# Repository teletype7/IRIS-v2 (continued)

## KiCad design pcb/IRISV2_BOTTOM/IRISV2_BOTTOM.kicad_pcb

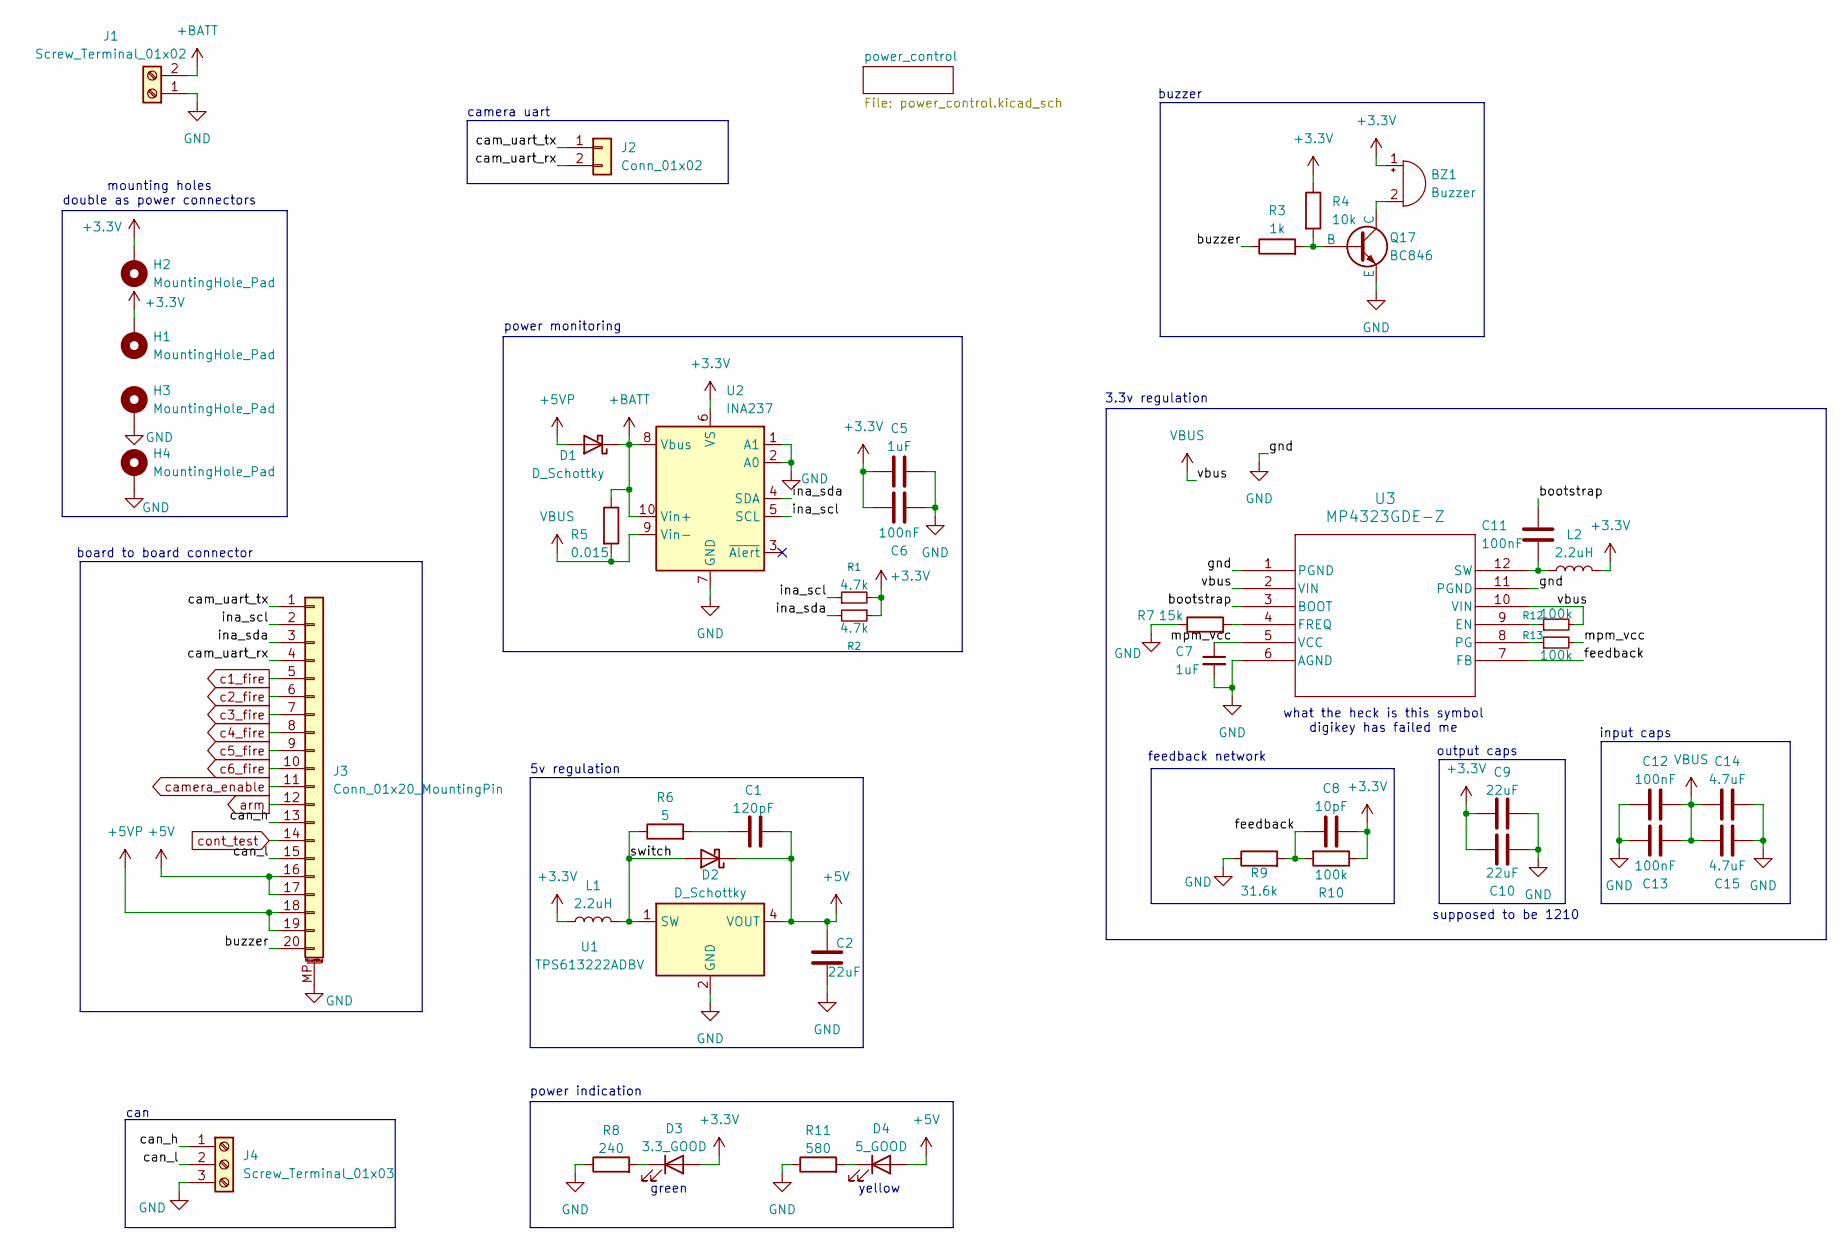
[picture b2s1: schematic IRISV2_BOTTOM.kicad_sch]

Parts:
BZ1: Buzzer; CMT850403SMTTR
C1: 120pF; C_0603_1608Metric
C2: 22uF; C_1206_3216Metric
C5, C7: 1uF; C_0603_1608Metric
C6: 100nF; C_0402_1005Metric
C8: 10pF; C_0402_1005Metric
C9, C10: 22uF; C_1210_3225Metric
C11, C12, C13: 100nF; C_0603_1608Metric
C14, C15: 4.7uF; C_1210_3225Metric
D1, D2: D_Schottky; DIOM5027X240N
D3: 3.3_GOOD; LED_0805_2012Metric
D4: 5_GOOD; LED_0805_2012Metric
H1, H2, H3, H4: MountingHole_Pad; MountingHole_3.2mm_M3_ISO7380_Pad_TopBottom
J1: Screw_Terminal_01x02; kf350-2p
J2: Conn_01x02; PinHeader_1x02_P2.54mm_Vertical
J3: Conn_01x20_MountingPin; FFC3B07-20-T
J4: Screw_Terminal_01x03; OSTTE030104
L1: 2.2uH; L_1008_2520Metric
L2: 2.2uH; SRP5020TA2R2M
Q17: BC846; SOT-23-3
R1, R2: 4.7k; R_0402_1005Metric
R3: 1k; R_0402_1005Metric
R4: 10k; R_0402_1005Metric
R5: 0.015; R_2512_6332Metric
R6: 5; R_0603_1608Metric
R7: 15k; R_0402_1005Metric
R8: 240; R_0603_1608Metric
R9: 31.6k; R_0402_1005Metric
R10, R12, R13: 100k; R_0402_1005Metric
R11: 580; R_0603_1608Metric
U1: TPS613222ADBV; SOT-23-5
U2: INA237; VSSOP-10_3x3mm_P0.5mm
U3: MP4323GDE-Z; QFN-12_MP4323_MNP

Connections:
+3.3V: BZ1.1 (+), C5.1, C6.2, C8.2, C9.1, C10.2, D3.2 (A), H1.1, H2.1, L1.1, L2.2, R1.2, R2.1, R4.1, R10.1, U2.6 (VS); also elsewhere on the board
+5V: C1.2, C2.1, D2.1 (K), D4.2 (A), J3.16, J3.17, U1.4 (VOUT)
+5VP: D1.2 (A), J3.18, J3.19
+BATT: D1.1 (K), J1.2, R5.1, U2.8 (Vbus), U2.10 (Vin+); also elsewhere on the board
/bootstrap: C11.1, U3.3 (BOOT)
/buzzer: J3.20, R3.1
/cam_uart_rx: J2.2, J3.4
/cam_uart_tx: J2.1, J3.1
/can_h: J3.13, J4.1
/can_l: J3.15, J4.2
/feedback: C8.1, R9.2, R10.2, U3.7 (FB)
/ina_scl: J3.2, R1.1, U2.5 (SCL)
/ina_sda: J3.3, R2.2, U2.4 (SDA)
/mpm_vcc: C7.1, R13.2, U3.5 (VCC)
/switch: D2.2 (A), L1.2, R6.1, U1.1 (SW)
GND: C2.2, C5.2, C6.1, C7.2, C9.2, C10.1, C12.1, C13.2, C14.2, C15.1, H3.1, H4.1, J1.1, J3.MP (MountPin), J4.3, Q17.3 (E), R7.1, R8.1, R9.1, R11.1, U1.2 (GND), U2.1 (A1), U2.2 (A0), U2.7 (GND), U3.1 (PGND), U3.6 (AGND), U3.11 (PGND); also elsewhere on the board
unnamed: BZ1.2 (-), Q17.1 (C)
unnamed: C1.1, R6.2
unnamed: D3.1 (K), R8.2
unnamed: D4.1 (K), R11.2
unnamed: Q17.2 (B), R3.2, R4.2
unnamed: R12.1, U3.9 (EN)
unnamed: R7.2, U3.4 (FREQ)
unnamed: R13.1, U3.8 (PG)
unnamed: C11.2, L2.1, U3.12 (SW)
VBUS: C12.2, C13.1, C14.1, C15.2, R5.2, R12.2, U2.9 (Vin-), U3.2 (VIN), U3.10 (VIN); also elsewhere on the board
arm: J3.12; also elsewhere on the board
c1_fire: J3.5; also elsewhere on the board
c2_fire: J3.6; also elsewhere on the board
c3_fire: J3.7; also elsewhere on the board
c4_fire: J3.8; also elsewhere on the board
c5_fire: J3.9; also elsewhere on the board
c6_fire: J3.10; also elsewhere on the board
camera_enable: J3.11; also elsewhere on the board
cont_test: J3.14; also elsewhere on the board

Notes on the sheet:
power monitoring
input caps
supposed to be 1210
power indication
camera uart
green
3.3v regulation
yellow
5v regulation
can
output caps
buzzer
board to board connector
what the heck is this symbol digikey has failed me
feedback network
mounting holes double as power connectors

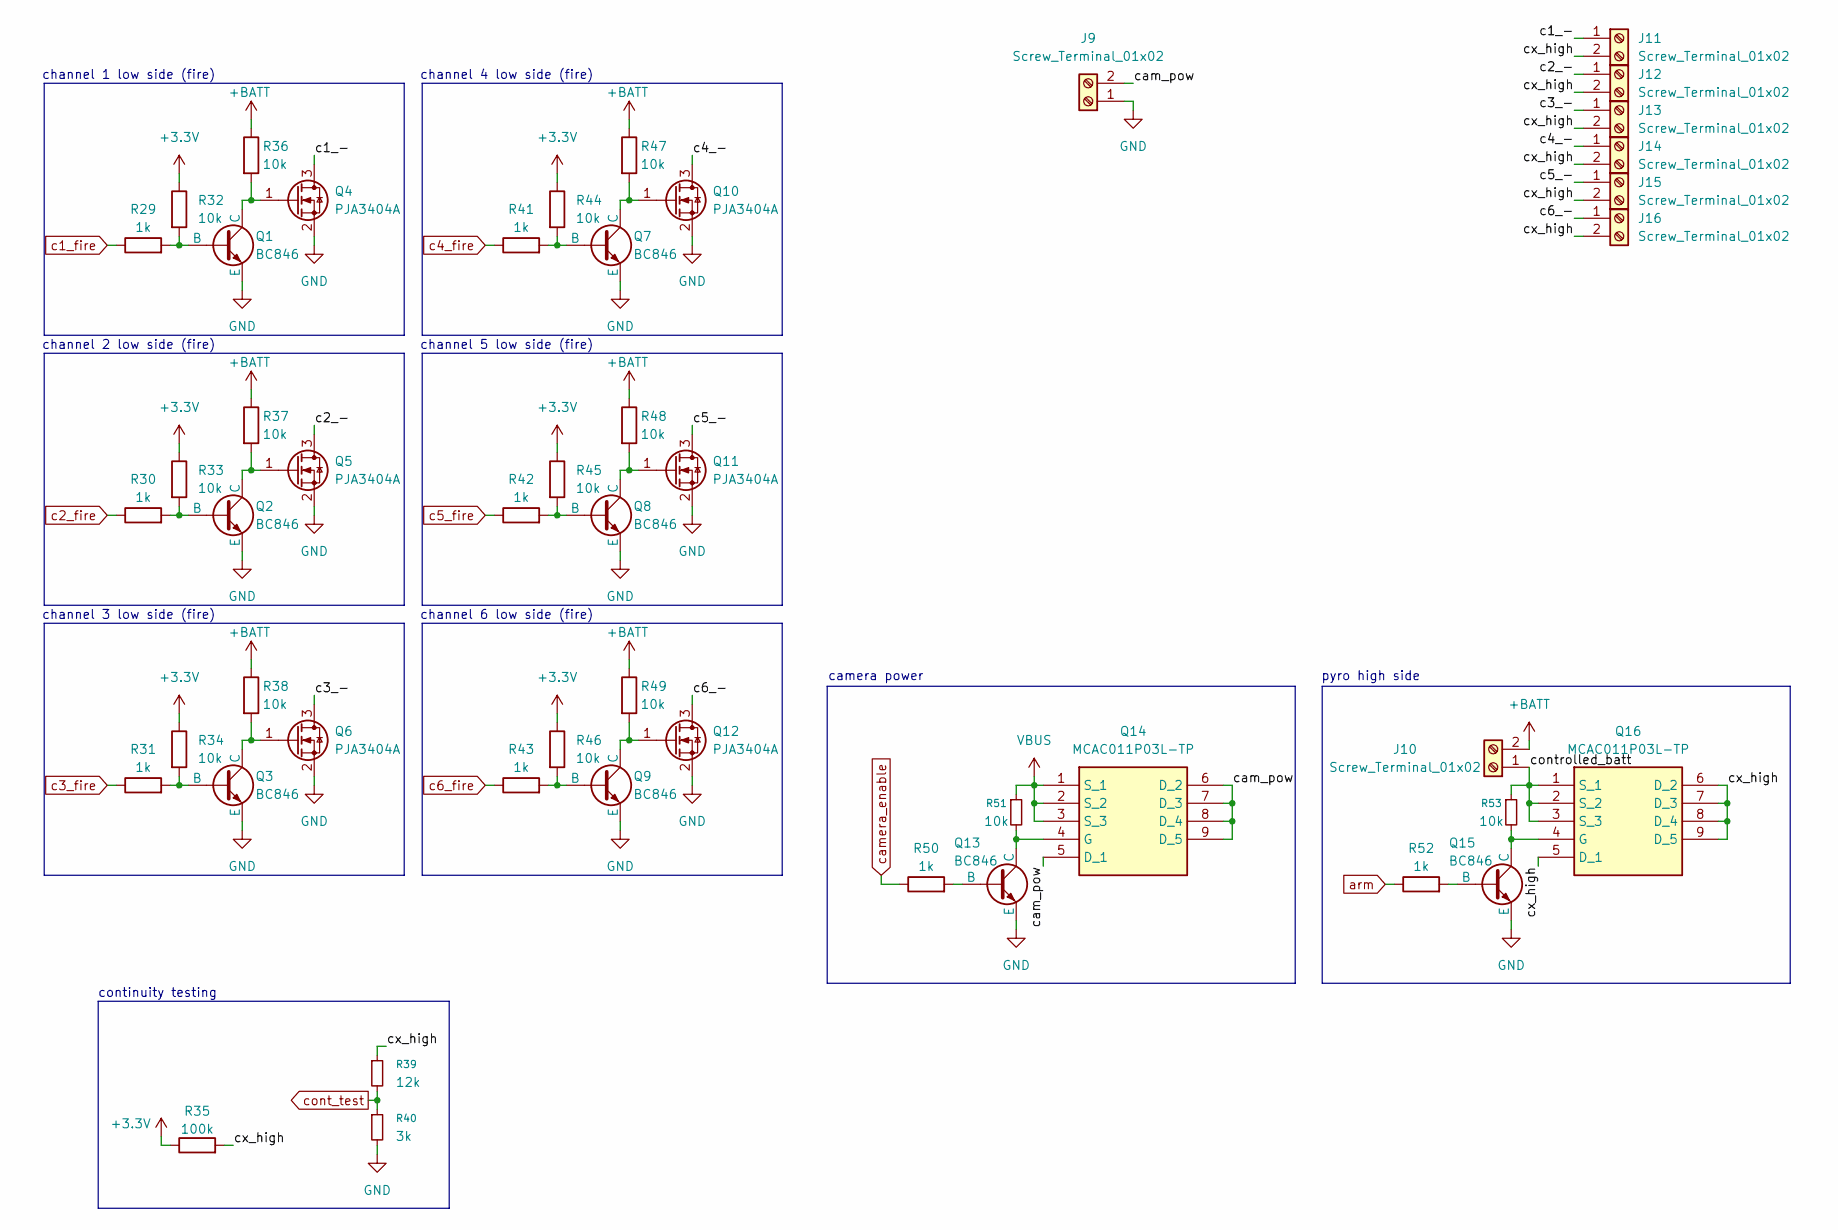
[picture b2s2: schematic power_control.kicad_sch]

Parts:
J9, J10, J11, J12, J13, J14, J15, J16: Screw_Terminal_01x02; kf350-2p
Q1, Q2, Q3, Q7, Q8, Q9, Q13, Q15: BC846; SOT-23-3
Q4, Q5, Q6, Q10, Q11, Q12: PJA3404A; SOT-23-3
Q14, Q16: MCAC011P03L-TP; MCAC100N08YATP; Manufacturer_Part_Number MCAC011P03L-TP
R29, R30, R31, R41, R42, R43, R50, R52: 1k; R_0402_1005Metric
R32, R33, R34, R36, R37, R38, R44, R45, R46, R47, R48, R49, R51, R53: 10k; R_0402_1005Metric
R35: 100k; R_0402_1005Metric
R39: 12k; R_0402_1005Metric
R40: 3k; R_0402_1005Metric

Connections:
+3.3V: R32.1, R33.1, R34.1, R35.1, R44.1, R45.1, R46.1; also elsewhere on the board
+BATT: J10.2, R36.1, R37.1, R38.1, R47.1, R48.1, R49.1; also elsewhere on the board
/power_control/c1_-: J11.1, Q4.3 (D)
/power_control/c2_-: J12.1, Q5.3 (D)
/power_control/c3_-: J13.1, Q6.3 (D)
/power_control/c4_-: J14.1, Q10.3 (D)
/power_control/c5_-: J15.1, Q11.3 (D)
/power_control/c6_-: J16.1, Q12.3 (D)
/power_control/cam_pow: J9.2, Q14.5 (D_1), Q14.6 (D_2), Q14.7 (D_3), Q14.8 (D_4), Q14.9 (D_5)
/power_control/controlled_batt: J10.1, Q16.1 (S_1), Q16.2 (S_2), Q16.3 (S_3), R53.1
/power_control/cx_high: J11.2, J12.2, J13.2, J14.2, J15.2, J16.2, Q16.5 (D_1), Q16.6 (D_2), Q16.7 (D_3), Q16.8 (D_4), Q16.9 (D_5), R35.2, R39.1
GND: J9.1, Q1.3 (E), Q2.3 (E), Q3.3 (E), Q4.2 (S), Q5.2 (S), Q6.2 (S), Q7.3 (E), Q8.3 (E), Q9.3 (E), Q10.2 (S), Q11.2 (S), Q12.2 (S), Q13.3 (E), Q15.3 (E), R40.2; also elsewhere on the board
unnamed: Q1.2 (B), R29.2, R32.2
unnamed: Q1.1 (C), Q4.1 (G), R36.2
unnamed: Q2.2 (B), R30.2, R33.2
unnamed: Q2.1 (C), Q5.1 (G), R37.2
unnamed: Q3.2 (B), R31.2, R34.2
unnamed: Q3.1 (C), Q6.1 (G), R38.2
unnamed: Q7.2 (B), R41.2, R44.2
unnamed: Q8.2 (B), R42.2, R45.2
unnamed: Q9.2 (B), R43.2, R46.2
unnamed: Q7.1 (C), Q10.1 (G), R47.2
unnamed: Q8.1 (C), Q11.1 (G), R48.2
unnamed: Q9.1 (C), Q12.1 (G), R49.2
unnamed: Q13.2 (B), R50.2
unnamed: Q13.1 (C), Q14.4 (G), R51.2
unnamed: Q15.2 (B), R52.2
unnamed: Q15.1 (C), Q16.4 (G), R53.2
VBUS: Q14.1 (S_1), Q14.2 (S_2), Q14.3 (S_3), R51.1; also elsewhere on the board
arm: R52.1; also elsewhere on the board
c1_fire: R29.1; also elsewhere on the board
c2_fire: R30.1; also elsewhere on the board
c3_fire: R31.1; also elsewhere on the board
c4_fire: R41.1; also elsewhere on the board
c5_fire: R42.1; also elsewhere on the board
c6_fire: R43.1; also elsewhere on the board
camera_enable: R50.1; also elsewhere on the board
cont_test: R39.2, R40.1; also elsewhere on the board

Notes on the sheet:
channel 6 low side (fire)
channel 2 low side (fire)
channel 1 low side (fire)
pyro high side
camera power
continuity testing
channel 4 low side (fire)
channel 5 low side (fire)
channel 3 low side (fire)

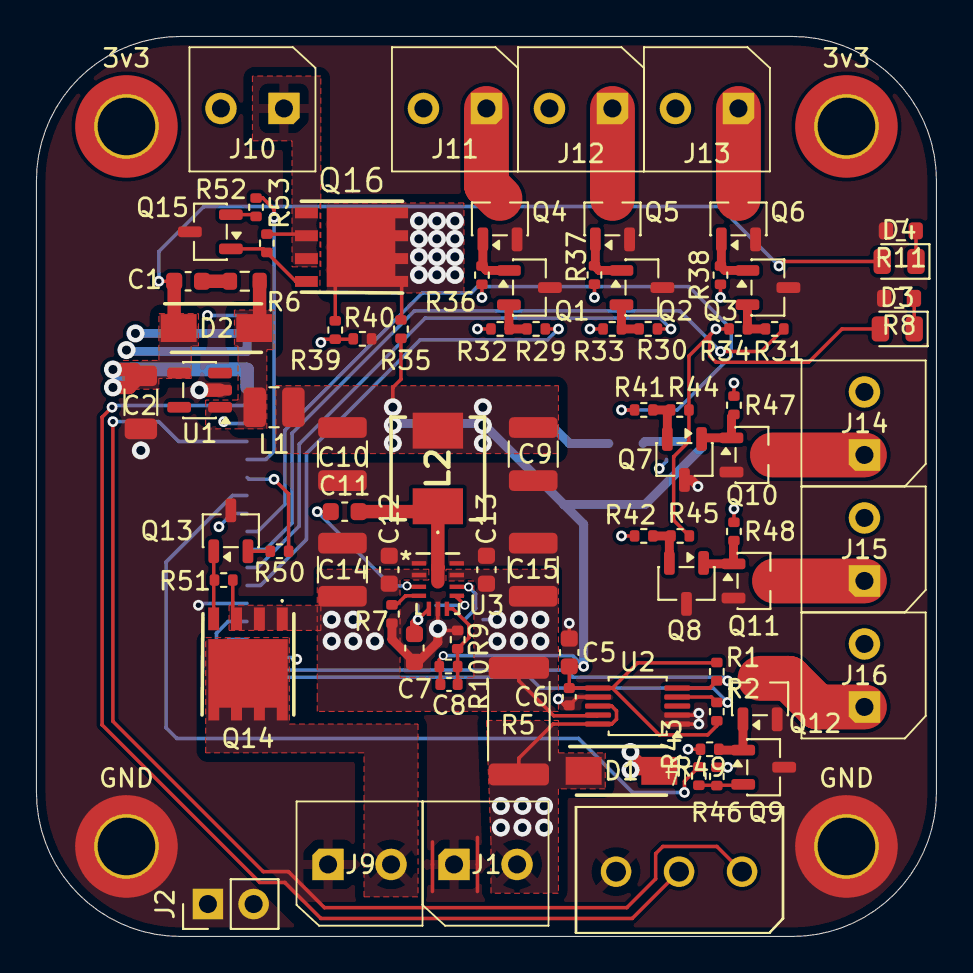
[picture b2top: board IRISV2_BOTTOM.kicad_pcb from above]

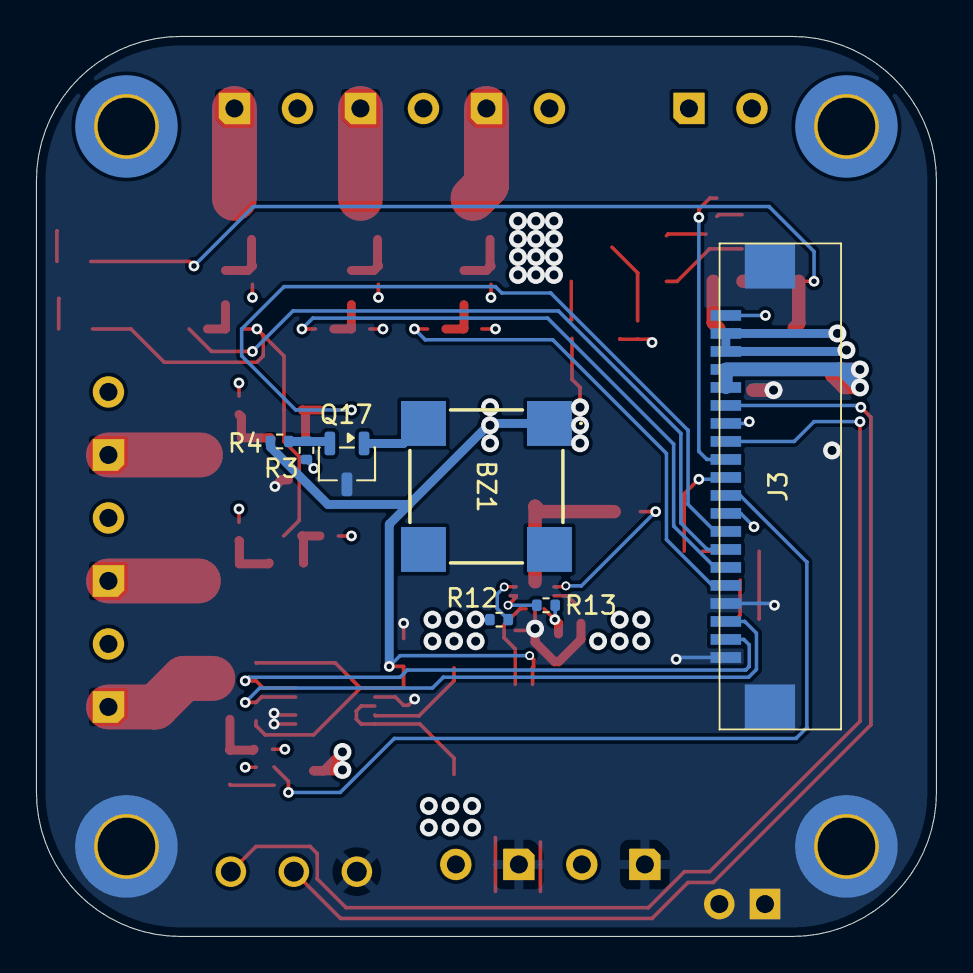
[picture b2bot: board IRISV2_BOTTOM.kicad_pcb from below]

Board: 4 copper layers, 50.0 x 50.0 mm, 94 parts (7 on the bottom side), 60 nets.

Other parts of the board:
3v3, 3v3#2: MountingHole_Pad; MountingHole_3.2mm_M3_ISO7380_Pad_TopBottom
GND: MountingHole_Pad; MountingHole_3.2mm_M3_ISO7380_Pad_TopBottom
GND#2: MountingHole_Pad; MountingHole_3.2mm_M3_ISO7380_Pad_TopBottom

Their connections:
+3.3V: 3v3.1, 3v3#2.1; also elsewhere on the board
GND: GND.1, GND#2.1; also elsewhere on the board

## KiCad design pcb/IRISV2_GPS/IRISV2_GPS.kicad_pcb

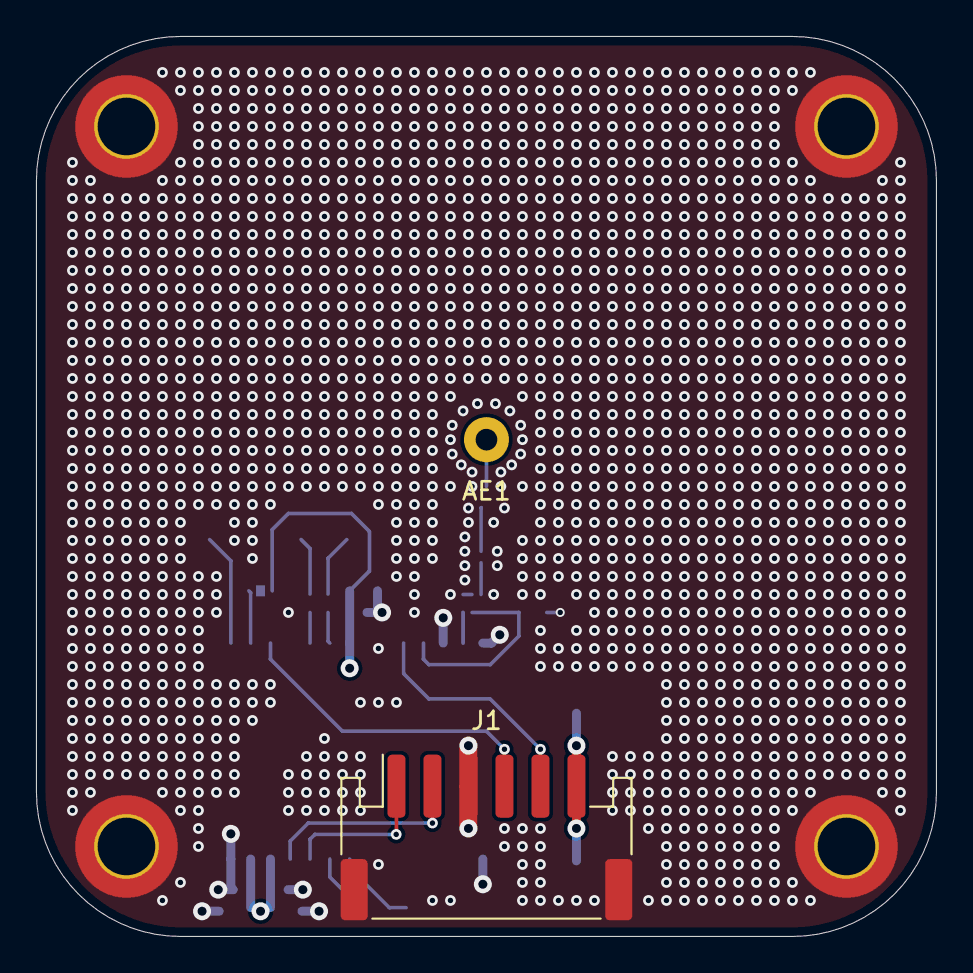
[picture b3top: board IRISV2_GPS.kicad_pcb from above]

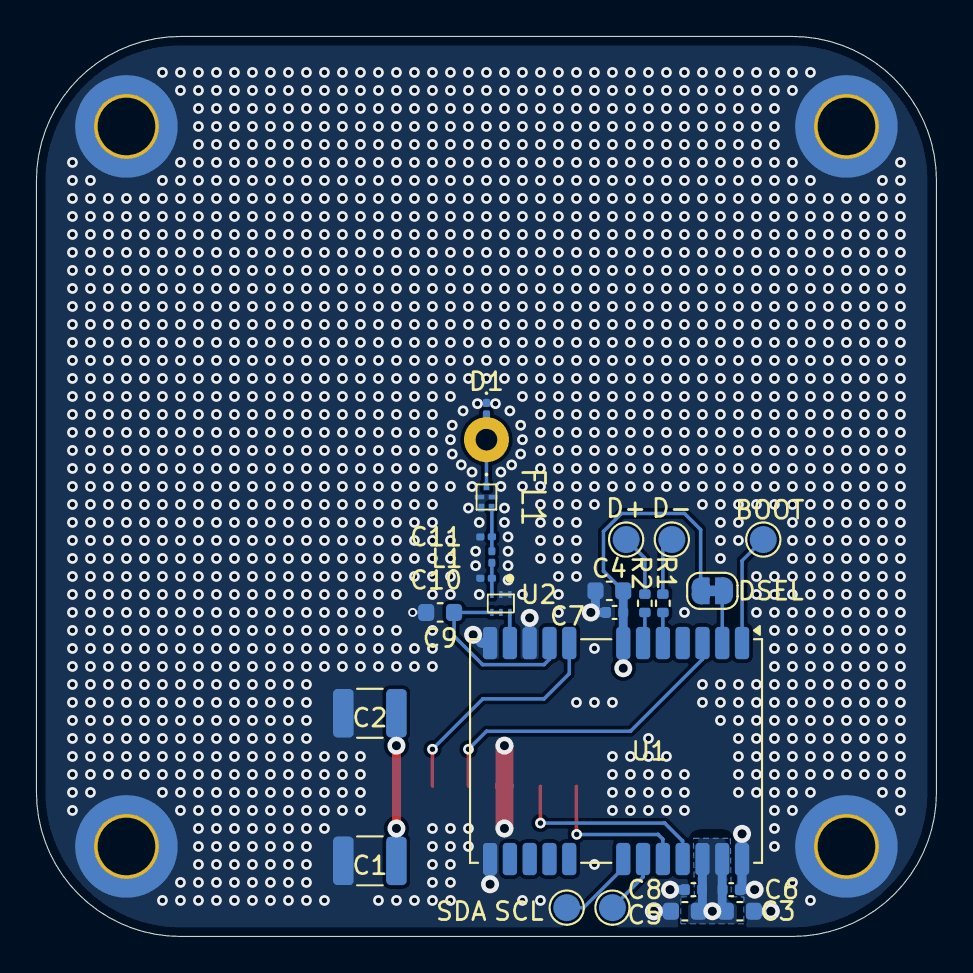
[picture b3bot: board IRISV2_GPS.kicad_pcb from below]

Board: 4 copper layers, 50.0 x 50.0 mm, 30 parts (24 on the bottom side), 19 nets.

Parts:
AE1: AANI-PP-0055
BOOT: GPS_BOOT; TestPoint_Pad_D1.5mm
C1, C2: 22uF; C_1210_3225Metric
C3, C4, C5, C9: 1uF; C_0603_1608Metric
C6, C7, C8: 100nF; C_0402_1005Metric
C10, C11: dnp; C_0201_0603Metric
D1: D_TVS; D_0201_0603Metric
D+: GPS_D+; TestPoint_Pad_D1.5mm
D-: GPS_D-; TestPoint_Pad_D1.5mm
DSEL: NC; SolderJumper-2_P1.3mm_Bridged_RoundedPad1.0x1.5mm
FL1: AFII-SW-0061-T; AFIISW0061T
H1, H2, H3, H4: MountingHole_Pad; MountingHole_3.2mm_M3_ISO7380_Pad_TopBottom
J1: Conn_01x06_MountingPin; JST_PH_S6B-PH-SM4-TB_1x06-1MP_P2.00mm_Horizontal
L1: 9.1nH; L_0201_0603Metric
R1, R2: 22; R_0402_1005Metric
SCL: GPS_SCL; TestPoint_Pad_D1.5mm
SDA: GPS_SDA; TestPoint_Pad_D1.5mm
U1: NEO-M9N; ublox_NEO
U2: lna; ALND-WB-0013-T

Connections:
+3.3V: C1.1, C2.1, C3.1, C4.1, C5.1, C6.1, C7.1, C8.1, DSEL.1 (A), J1.6, U1.7 (VDD_USB), U1.22 (V_BCKP), U1.23 (VCC)
GND: C1.2, C2.2, C3.2, C4.2, C5.2, C6.2, C7.2, C8.2, C9.2, C10.1, C11.2, D1.1 (A1), FL1.2 (GND), H1.1, H2.1, H3.1, H4.1, J1.3, J1.MP (MountPin), U1.10 (GND), U1.12 (GND), U1.13 (GND), U1.24 (GND), U2.1 (GND), U2.2 (GND)
unnamed: AE1.1 (A), D1.2 (A2), FL1.1 (INPUT)
unnamed: C11.1, FL1.4 (OUTPUT), L1.2
unnamed: DSEL.2 (B), U1.2 (D_SEL)
unnamed: D-.1, R1.1
unnamed: D+.1, R2.2
unnamed: U1.11 (RF_IN), U2.6 (RFOUT)
unnamed: SCL.1, U1.19 (SCL/SPI_CLK)
unnamed: SDA.1, U1.18 (SDA/~SPI_CS)
unnamed: R1.2, U1.5 (USB_DM)
unnamed: R2.1, U1.6 (USB_DP)
unnamed: C9.1, U1.9 (VCC_RF), U2.4 (VDD), U2.5 (Ven)
unnamed: BOOT.1, U1.1 (~SAFEBOOT)
unnamed: C10.2, L1.1, U2.3 (RFIN)
gps_mrx: J1.1, U1.20 (TXD/SPI_MISO)
gps_mtx: J1.2, U1.21 (RXD/SPI_MOSI)
gps_pps: J1.4, U1.3 (TIMEPULSE)
gps_rst: J1.5, U1.8 (~RESET)

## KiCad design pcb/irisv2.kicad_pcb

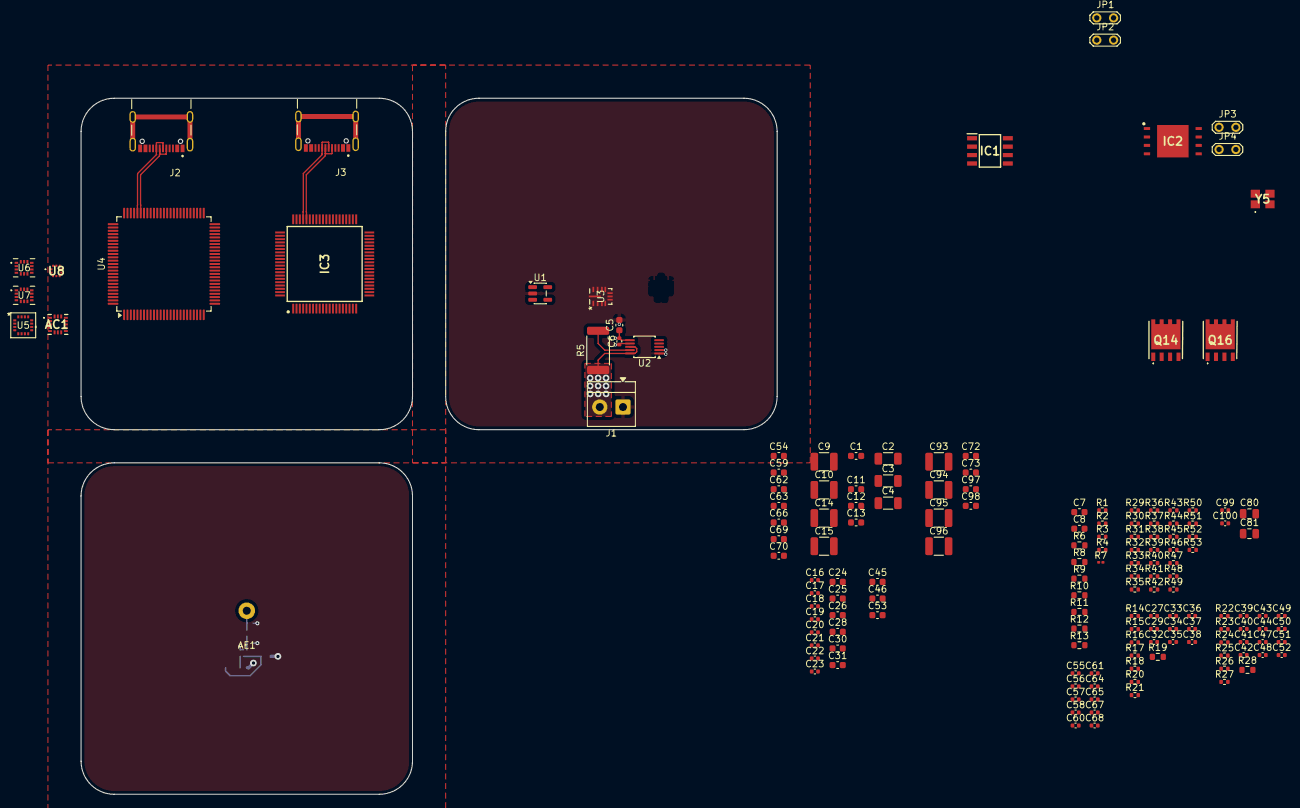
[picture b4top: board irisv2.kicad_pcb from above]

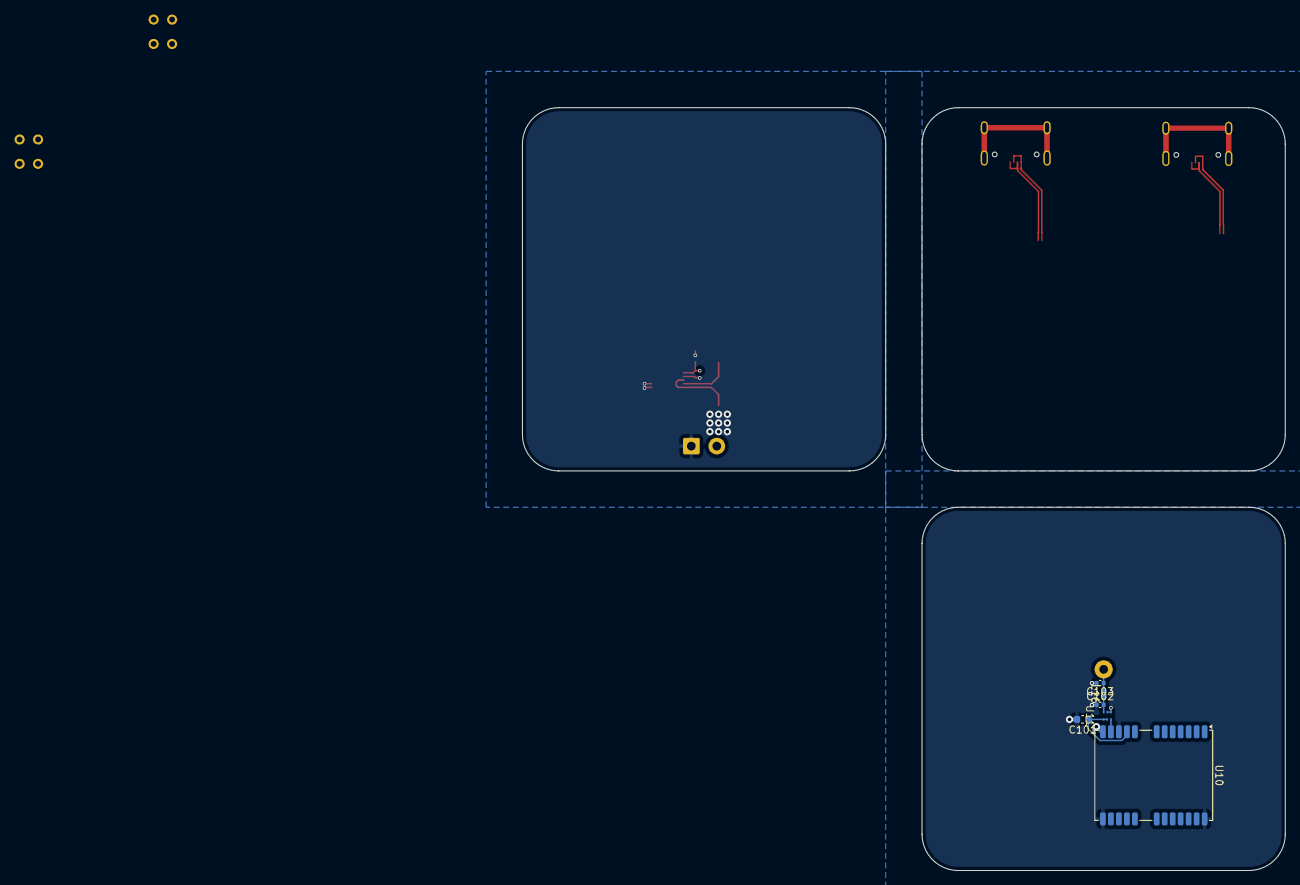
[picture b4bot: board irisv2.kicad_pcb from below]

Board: 6 copper layers, 105.0 x 105.0 mm, 164 parts (6 on the bottom side), 110 nets.

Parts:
AC1: H3LIS331DLTR; LIS3DHTR
AE1: AANI-PP-0055
C1: 120pF; C_0603_1608Metric
C2, C3, C4: 10uF; C_1206_3216Metric
C5, C7, C26, C28, C31, C45, C59, C62, C63, C66, C72, C73, C98, C101: 1uF; C_0603_1608Metric
C6, C18, C19, C22, C27, C29, C32, C33, C34, C35, C36, C37, C38, C43, C44, C47, C48, C49, C50, C51, C52, C55, C56, C57, C58, C60, C61, C64, C65, C67, C68, C99, C100: 100nF; C_0402_1005Metric
C8: 10pF; C_0603_1608Metric
C9, C10, C93, C94, C95, C96: 22uF; C_1210_3225Metric
C11, C12, C13: 100nF; C_0603_1608Metric
C14, C15: 4.7uF; C_1210_3225Metric
C16, C20, C39, C41: 8pF; C_0402_1005Metric
C17, C21, C40, C42: 17pF; C_0402_1005Metric
C23: 4.7nF; C_0402_1005Metric
C24, C25, C46: 2.2uF; C_0603_1608Metric
C30, C53, C97: 4.7uF; C_0603_1608Metric
C54, C69, C70: 10uF; C_0603_1608Metric
C80, C81: 2.2uF; C_0805_2012Metric
C102, C103: dnp; C_0402_1005Metric
IC1: ATA6561-GAQW-N; SOIC127P600X175-8N
IC2: S25FL256LAGNFI010; SON127P800X600X80-9N-D
IC3: STM32C552MET6; QFP50P1400X1400X160-80N
J1: Screw_Terminal_01x02; TerminalBlock_MetzConnect_Type059_RT06302HBWC_1x02_P3.50mm_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
J2, J3: USB_C_Receptacle_USB2.0_16P; SAMESKY_UJ20-C-H-G-SMT-1-P16-TR
JP1, JP3: BOOT; TestPoint_2Pads_Pitch2.54mm_Drill0.8mm
JP2, JP4: RST; TestPoint_2Pads_Pitch2.54mm_Drill0.8mm
L16: 9.1nH; L_0402_1005Metric
Q14, Q16: MCAC011P03L-TP; MCAC100N08YATP
R1, R2, R3, R4: 5.1k; R_0402_1005Metric
R5: 0.015; R_2512_6332Metric
R6: 5; R_0603_1608Metric
R7: 15k; R_0201_0603Metric
R8: 240; R_0603_1608Metric
R9: 31.6k; R_0603_1608Metric
R10, R12, R13: 100k; R_0603_1608Metric
R11: 580; R_0603_1608Metric
R14, R15, R16, R22, R23, R24, R25, R32, R33, R34, R36, R37, R38, R44, R45, R46, R47, R48, R49, R51, R53: 10k; R_0402_1005Metric
R17, R18: 60; R_0402_1005Metric
R19, R28: 120; R_0603_1608Metric
R20, R21, R26, R27, R29, R30, R31, R41, R42, R43, R50, R52: 1k; R_0402_1005Metric
R35: 100k; R_0402_1005Metric
R39: 12k; R_0402_1005Metric
R40: 3k; R_0402_1005Metric
U1: TPS613222ADBV; SOT-23-5
U2: INA237; VSSOP-10_3x3mm_P0.5mm
U3: MP4323GDE-Z; QFN-12_MP4323_MNP
U4: STM32H563VITx; LQFP-100_14x14mm_P0.5mm
U5: MMC5983MA; MMC5983MA_MEM
U6, U7: ICM-45686; U_2p5X3X0p81_LGA14L_TDK
U8: BMP581
U10: NEO-M9N; ublox_NEO
U11: lna; ALND-WB-0013-T
Y5: ECS-TXO-32CSMV-320-AN-TR; ECSTXO32CSMV320ANTR

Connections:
+3.3V: AC1.1 (VDD_IO), AC1.14 (VDD), C5.1, C6.2, C8.2, C9.1, C10.2, C19.1, C26.1, C27.1, C28.1, C29.1, C30.1, C31.1, C32.1, C33.1, C34.1, C35.1, C36.1, C37.1, C38.1, C44.1, C45.1, C47.1, C48.1, C49.1, C50.1, C51.1, C52.1, C53.1, C55.1, C56.1, C57.1, C58.1, C59.1, C60.1, C61.1, C62.1, C63.1, C64.1, C65.1, C66.1, C67.1, C68.1, C69.1, C70.1, C93.1, C94.1, IC1.5 (VIO), IC2.8 (VCC), IC3.7 (VDD_1), IC3.16 (VREF+), IC3.23 (VDD_2), IC3.40 (VDD_3), IC3.60 (VDD_4), IC3.80 (VDD_5), JP1.1 (A), JP3.1 (A), R10.1, R15.1, R22.1, R24.1, R32.1, R33.1, R34.1, R35.1, R44.1, R45.1, R46.1, U2.6 (VS), U4.6 (VBAT), U4.11 (VDD), U4.21 (VREF+), U4.22 (VDDA), U4.28 (VDD), U4.50 (VDD), U4.73 (VDDUSB), U4.75 (VDD), U4.100 (VDD), U5.2 (VDD), U5.13 (VDDIO), U6.5 (VDDIO), U6.8 (VDD), U7.5 (VDDIO), U7.8 (VDD), U8.1 (VDDIO), U8.10 (VDD), U10.7 (VDD_USB), U10.22 (V_BCKP), U10.23 (VCC)
+5V: C1.2, C2.1, C3.1, C4.1, C22.1, IC1.3 (VCC), U1.4 (VOUT)
+5VP: J2.A4 (VBUS), J3.A4 (VBUS)
+BATT: J1.2, R5.1, R36.1, R37.1, R38.1, R47.1, R48.1, R49.1, U2.8 (Vbus), U2.10 (Vin+)
/bootstrap: C11.1, U3.3 (BOOT)
/feedback: R9.1, U3.7 (FB)
/fets/cam_pow: Q14.5 (D_1), Q14.6 (D_2), Q14.7 (D_3), Q14.8 (D_4), Q14.9 (D_5)
/fets/cx_high: Q16.5 (D_1), Q16.6 (D_2), Q16.7 (D_3), Q16.8 (D_4), Q16.9 (D_5), R35.2, R39.1
/main_mcu/boot: R16.2, U4.94 (BOOT0)
/main_mcu/can_h: IC1.7 (CANH), R17.1
/main_mcu/can_l: IC1.6 (CANL), R18.2
/main_mcu/can_rx: IC1.4 (RXD), U4.81 (PD0)
/main_mcu/can_stby: IC1.8 (STBY), U4.83 (PD2)
/main_mcu/can_tx: IC1.1 (TXD), U4.82 (PD1)
/main_mcu/hse_0: C16.2, U4.12 (PH0)
/main_mcu/hse_1: C20.1, R20.1
/main_mcu/lse_0: C17.2, U4.8 (PC14)
/main_mcu/lse_1: C21.1, R21.2
/main_mcu/rst: C18.1, JP2.2 (B), R15.2, U4.14 (NRST)
/mpm_vcc: C7.1, R13.2, U3.5 (VCC)
/peripheral_mcu/boot: IC3.74 (PH2-BOOT0), R25.2
/peripheral_mcu/flash_clk: IC2.6 (SCK), IC3.42 (PB13)
/peripheral_mcu/flash_cs: IC2.1 (CS#), R22.2
/peripheral_mcu/flash_miso: IC2.2 (SO/IO1), IC3.43 (PB14)
/peripheral_mcu/flash_mosi: IC2.5 (SI/IO0), IC3.44 (PB15)
/peripheral_mcu/hse_0: C39.2, IC3.8 (PH0-OSC_IN)
/peripheral_mcu/hse_1: C41.1, R27.1
/peripheral_mcu/lse_0: C40.2, IC3.4 (PC14-OSC32_IN)
/peripheral_mcu/lse_1: C42.1, R26.2
/peripheral_mcu/rst: C43.1, IC3.10 (NRST), JP4.2 (B), R24.2
/rf/lr2021_vbat: C95.1, C96.1, C97.1, C98.1, C99.1, C100.1
/rf/lr2021_vdcc: C72.1, C73.1
/rf/lr2021_vpax: C80.1, C81.1
GND: AC1.5 (GND_1), AC1.12 (GND_2), AC1.13 (GND_3), AC1.16 (GND_4), C2.2, C3.2, C4.2, C5.2, C6.1, C7.2, C9.2, C10.1, C12.1, C13.2, C14.2, C15.1, C16.1, C17.1, C18.2, C19.2, C20.2, C21.2, C22.2, C23.1, C24.1, C25.1, C26.2, C27.2, C28.2, C29.2, C30.2, C31.2, C32.2, C33.2, C34.2, C35.2, C36.2, C37.2, C38.2, C39.1, C40.1, C41.2, C42.2, C43.2, C44.2, C45.2, C46.2, C47.2, C48.2, C49.2, C50.2, C51.2, C52.2, C53.2, C54.2, C55.2, C56.2, C57.2, C58.2, C59.2, C60.2, C61.2, C62.2, C63.2, C64.2, C65.2, C66.2, C67.2, C68.2, C69.2, C70.2, C72.2, C73.2, C80.2, C81.2, C93.2, C94.2, C95.2, C96.2, C97.2, C98.2, C99.2, C100.2, C101.2, C102.1, C103.2, IC1.2 (GND), IC2.4 (VSS), IC2.9 (EP), IC3.6 (VSS_1), IC3.15 (VREF-), IC3.22 (VSS_2), IC3.39 (VSS_3), IC3.59 (VSS_4), IC3.79 (VSS_5), J1.1, J2.A1 (GND), J3.A1 (GND), JP2.1 (A), JP4.1 (A), R1.2, R2.1, R3.2, R4.1, R7.1, R8.1, R11.1, R14.2, R19.1, R23.2, R28.1, R40.2, U1.2 (GND), U2.1 (A1), U2.2 (A0), U2.7 (GND), U3.1 (PGND), U3.6 (AGND), U3.11 (PGND), U4.10 (VSS), U4.19 (VSSA), U4.20 (VREF-), U4.27 (VSS), U4.49 (VSS), U4.74 (VSS), U4.99 (VSS), U5.9 (GND), U5.11 (GND), U6.6 (GND), U7.6 (GND), U8.3 (VSS_1), U8.8 (VSS_2), U8.9 (VSS_3), U10.10 (GND), U10.12 (GND), U10.13 (GND), U10.24 (GND), U11.1 (GND), U11.2 (GND), Y5.1 (GROUND_1), Y5.2 (GROUND_2)
unnamed: AE1.1 (A), C103.1, L16.2
unnamed: C1.1, R6.2
unnamed: C8.1, R9.2, R10.2
unnamed: C23.2, R17.2, R18.1
unnamed: C24.2, C25.2, U4.48 (VCAP), U4.98 (VCAP)
unnamed: R6.1, U1.1 (SW)
unnamed: IC3.5 (PC15-OSC32_OUT), R26.1
unnamed: IC3.9 (PH1-OSC_OUT), R27.2
unnamed: C46.1, IC3.38 (VCAP)
unnamed: J2.A5 (CC1), R1.1
unnamed: J2.B5 (CC2), R2.2
unnamed: J3.A5 (CC1), R3.1
unnamed: J3.B5 (CC2), R4.2
unnamed: Q16.1 (S_1), Q16.2 (S_2), Q16.3 (S_3), R53.1
unnamed: JP1.2 (B), R14.1, R16.1
unnamed: JP3.2 (B), R23.1, R25.1
unnamed: R29.2, R32.2
unnamed: R30.2, R33.2
unnamed: R31.2, R34.2
unnamed: R41.2, R44.2
unnamed: R42.2, R45.2
unnamed: R43.2, R46.2
unnamed: Q14.4 (G), R51.2
unnamed: Q16.4 (G), R53.2
unnamed: R12.1, U3.9 (EN)
unnamed: R7.2, U3.4 (FREQ)
unnamed: R13.1, U3.8 (PG)
unnamed: C11.2, U3.12 (SW)
unnamed: R21.1, U4.9 (PC15)
unnamed: R20.2, U4.13 (PH1)
unnamed: C54.1, U5.10 (CAP)
unnamed: U10.11 (RF_IN), U11.6 (RFOUT)
unnamed: C101.1, U10.9 (VCC_RF), U11.4 (VDD), U11.5 (Ven)
unnamed: C102.2, L16.1, U11.3 (RFIN)
VBUS: C12.2, C13.1, C14.1, C15.2, Q14.1 (S_1), Q14.2 (S_2), Q14.3 (S_3), R5.2, R12.2, R51.1, U2.9 (Vin-), U3.2 (VIN), U3.10 (VIN)
arm: IC3.53 (PA8), R52.1
bmp_cs: U4.84 (PD3), U8.6 (CSB)
bmp_int: U4.85 (PD4), U8.7 (INT)
bmp_miso: U4.79 (PC11), U8.5 (SDO)
bmp_mosi: U4.80 (PC12), U8.4 (SDI)
bmp_sck: U4.78 (PC10), U8.2 (SCK)
c1_fire: IC3.52 (PC9), R29.1
c2_fire: IC3.51 (PC8), R30.1
c3_fire: IC3.50 (PC7), R31.1
c4_fire: IC3.49 (PC6), R41.1
c5_fire: IC3.48 (PD15), R42.1
c6_fire: IC3.47 (PD14), R43.1
camera_enable: IC3.46 (PD13), R50.1
cont_test: IC3.18 (PA0), R39.2, R40.1
gps_mrx: U4.56 (PD9), U10.20 (TXD/SPI_MISO)
gps_mtx: U4.55 (PD8), U10.21 (RXD/SPI_MOSI)
icm1_cs: U4.46 (PE15), U6.12 (AP_CS)
icm1_int: U4.45 (PE14), U6.4 (INT1/INT)
icm1_miso: U4.53 (PB14), U6.1 (AP_SDO/AP_AD0)
icm1_mosi: U4.54 (PB15), U6.14 (AP_SDA/AP_SDIO/AP_SDI)
icm1_sck: U4.52 (PB13), U6.13 (AP_SCL/AP_SCLK)
icm2_cs: U4.33 (PC4), U7.12 (AP_CS)
icm2_int: U4.34 (PC5), U7.4 (INT1/INT)
icm2_miso: U4.31 (PA6), U7.1 (AP_SDO/AP_AD0)
icm2_mosi: U4.32 (PA7), U7.14 (AP_SDA/AP_SDIO/AP_SDI)
icm2_sck: U4.30 (PA5), U7.13 (AP_SCL/AP_SCLK)
icm_fsync: U4.60 (PD13), U6.9 (INT2/FSYNC/CLKIN), U7.9 (INT2/FSYNC/CLKIN)
ina_scl: IC3.72 (PB6), U2.5 (SCL)
ina_sda: IC3.73 (PB7), U2.4 (SDA)
mag_cs: U4.3 (PE4), U5.4 (SPI_CS)
mag_int: U4.2 (PE3), U5.15 (INT)
mag_miso: U4.4 (PE5), U5.5 (SPI_SDO)
mag_mosi: U4.5 (PE6), U5.16 (SDA/SPI_SDI)
mag_sck: U4.1 (PE2), U5.1 (SCL/SPI_SCK)
mcu->ppu_miso: IC3.27 (PA7), U4.90 (PB4(NJTRST))
mcu->ppu_mosi: IC3.26 (PA6), U4.91 (PB5)
mcu->ppu_sck: IC3.25 (PA5), U4.89 (PB3(JTDO)
usb1_d+: J2.A6 (D+), J2.B6 (D+), U4.71 (PA12)
usb1_d-: J2.A7 (D-), J2.B7 (D-), U4.70 (PA11)
usb2_d+: IC3.57 (PA12), J3.A6 (D+), J3.B6 (D+)
usb2_d-: IC3.56 (PA11), J3.A7 (D-), J3.B7 (D-)

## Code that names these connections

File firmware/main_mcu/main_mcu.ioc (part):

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Mcu.Name=STM32H563VITx
Mcu.Package=LQFP100
Mcu.UserName=STM32H563VITx
PA0.Signal=S_TIM2_CH1
PA1.Signal=S_TIM2_CH2
PA10.Mode=Asynchronous
PA10.Signal=USART1_RX
PA11.Mode=Device
PA11.Signal=USB_DM
PA12.Mode=Device
PA12.Signal=USB_DP
PA13(JTMS/SWDIO).Mode=Serial_Wire
PA13(JTMS/SWDIO).Signal=DEBUG_JTMS-SWDIO
PA14(JTCK/SWCLK).Mode=Serial_Wire
PA14(JTCK/SWCLK).Signal=DEBUG_JTCK-SWCLK
PA15(JTDI).Mode=NSS_Signal_Hard_Output
PA15(JTDI).Signal=SPI3_NSS
PA2.Signal=S_TIM2_CH3
PA3.Signal=S_TIM2_CH4
PA4.Mode=NSS_Signal_Hard_Output
PA4.Signal=SPI1_NSS
PA5.Mode=Full_Duplex_Master
PA5.Signal=SPI1_SCK
PA6.Mode=Full_Duplex_Master
PA6.Signal=SPI1_MISO
PA7.Mode=Full_Duplex_Master
PA7.Signal=SPI1_MOSI
PA9.Mode=Asynchronous
PA9.Signal=USART1_TX
PB12.Mode=NSS_Signal_Hard_Output
PB12.Signal=SPI2_NSS
PB13.Mode=Full_Duplex_Master
PB13.Signal=SPI2_SCK
PB14.Mode=Full_Duplex_Master
PB14.Signal=SPI2_MISO
PB15.Mode=Full_Duplex_Master
PB15.Signal=SPI2_MOSI
PB3(JTDO/TRACESWO).Mode=Full_Duplex_Master
PB3(JTDO/TRACESWO).Signal=SPI6_SCK
PB4(NJTRST).Mode=Full_Duplex_Master
PB4(NJTRST).Signal=SPI6_MISO
PB5.Mode=Full_Duplex_Master
PB5.Signal=SPI6_MOSI
PB7.Mode=I2C
PB7.Signal=I2C1_SDA
PB8.Mode=I2C
PB8.Signal=I2C1_SCL
PC10.Mode=Full_Duplex_Master
PC10.Signal=SPI3_SCK
PC11.Mode=Full_Duplex_Master
PC11.Signal=SPI3_MISO
PC12.Mode=Full_Duplex_Master
PC12.Signal=SPI3_MOSI
PC14-OSC32_IN(OSC32_IN).Mode=LSE-External-Oscillator
PC14-OSC32_IN(OSC32_IN).Signal=RCC_OSC32_IN
PC15-OSC32_OUT(OSC32_OUT).Mode=LSE-External-Oscillator
PC15-OSC32_OUT(OSC32_OUT).Signal=RCC_OSC32_OUT
PC4.Signal=GPXTI4
PC6.Signal=S_TIM3_CH1
PC7.Signal=S_TIM3_CH2
PC8.Signal=S_TIM3_CH3
PC9.Signal=S_TIM3_CH4
PD0.Mode=FDCAN_Activate
PD0.Signal=FDCAN1_RX
PD1.Mode=FDCAN_Activate
PD1.Signal=FDCAN1_TX
PD10.Signal=GPXTI10
PD11.Mode=Asynchronous
PD11.Signal=UART4_RX
PD12.Mode=Asynchronous
PD12.Signal=UART4_TX
PD2.Signal=GPXTI2
PD3.Signal=GPIO_Output
PD5.Mode=Asynchronous
PD5.Signal=USART2_TX
PD6.Mode=Asynchronous
PD6.Signal=USART2_RX
PD8.Mode=Asynchronous
PD8.Signal=USART3_TX
PD9.Mode=Asynchronous
PD9.Signal=USART3_RX
PE0.Signal=GPIO_Output
PE14.Signal=S_TIM1_CH4
PE2.Mode=Full_Duplex_Master
PE2.Signal=SPI4_SCK
PE3.Signal=GPXTI3
PE4.Mode=NSS_Signal_Hard_Output
PE4.Signal=SPI4_NSS
PE5.Mode=Full_Duplex_Master
PE5.Signal=SPI4_MISO
PE6.Mode=Full_Duplex_Master
PE6.Signal=SPI4_MOSI
PH0-OSC_IN(PH0).Mode=HSE-External-Oscillator
PH0-OSC_IN(PH0).Signal=RCC_OSC_IN
PH1-OSC_OUT(PH1).Mode=HSE-External-Oscillator
PH1-OSC_OUT(PH1).Signal=RCC_OSC_OUT
RCC.HSE_VALUE=25000000
RCC.SYSCLKFreq_VALUE=250000000
RCC.SYSCLKSource=RCC_SYSCLKSOURCE_PLLCLK
board=custom

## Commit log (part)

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2026-04-11 initial - schematic work done, main mcu pinout started
2026-04-11 fixed super minor issues
2026-04-13 tons of work on rf and mcu
2026-04-16 added missing files, rf stuff done I think (hope)
2026-04-20 sensors pretty much done (still need to add high g_
2026-04-21 got fets figured out (finally), can integrated, a 5v regulator, sensors added - overall great progress!
2026-05-10 pretty much everything on schem done, though need to add circuit protection stuff and break out remaining pins
2026-05-11 yay schematic pretty much good, though I'm going to have to redo some work to split it into multiple kicad projects so I can have multiple separate boards
2026-05-12 split into subprojects, fixed up stuff, started real pcb work
2026-05-24 bottom pcb now mostly done, connectors selected - now need to finish integrating the connectors and other small tweaks to bottom routing
2026-05-24 bottom board design done, need to polish it
2026-05-24 bottom board pending sanity check but done
2026-05-25 gps finished minus tvs (WHY ARE THEY ALL 0201), top layout + routing started
2026-05-26 removed high g accel, top board layout looking decent, routing started also - though i realized i was missing the micro sd card and that's going to be a pain to add
2026-05-26 layout pretty much done, lr2021 rf stuff done, mostly just routing left
